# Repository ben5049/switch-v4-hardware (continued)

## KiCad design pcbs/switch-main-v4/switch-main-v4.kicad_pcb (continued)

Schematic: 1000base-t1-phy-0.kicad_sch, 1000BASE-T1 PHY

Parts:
C1301, C1302, C1305, C1306, C1307: 4u7; C_0402
C1303: 22p; C_0402
C1304, C1308, C1309, C1310, C1311, C1313, C1314, C1315, C1316, C1317, C1318, C1319, C1320: 100n; C_0402
C1312, C1321: 10u; C_0402
C1322: 10u; C_0402; not fitted
L1301: 78438313015; L_Wurth_WE-MAIA-1610; Part Number 78438313015
Q1301: DMN21D2UFB-7B; DMN21D2UFB7B; Mouser Part Number 621-DMN21D2UFB-7B
Q1302: DMP21D0UFB-7B; DMP21D0UFB7B; Mouser Part Number 621-DMP21D0UFB-7B
R1301, R1310: 4k7; R_0402
R1302: 10k; R_0402; not fitted
R1304: 4k7; R_0402; not fitted
R1305: 180k; R_0402
R1306: 360k; R_0402
R1307: 4k99; R_0402
R1308: 1k; R_0402
R1309: 47k; R_0402
TP1301, TP1302: 1.5mm; TestPoint_Pad_D1.5mm
U1301: TPS62290TDRVRQ1; SON65P200X200X80-7N; Mouser Part Number 595-TPS62290TDRVRQ1
U1302: 88Q2112-A2-NYD2A000-P123; 88Q2112

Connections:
+1V8: C1309.1, C1311.1, C1312.1, C1313.1, C1315.1, C1317.1, C1319.1, C1321.1, R1302.2, U1302.9 (AVDD18), U1302.24 (VDDO), U1302.33 (AVDD18), U1302.40 (VDDO); also elsewhere on the board
+3V3: C1301.1, C1302.1, C1308.1, C1310.1, U1301.2 (MODE), U1301.5 (VIN), U1302.6 (AVDD33); also elsewhere on the board
+3V3_AON: C1314.1, Q1302.2 (S), R1309.2, U1302.46 (VLPR); also elsewhere on the board
/CDNs & PoDL/MDI0_IN.TRXN: U1302.5 (MDIN); also elsewhere on the board
/CDNs & PoDL/MDI0_IN.TRXP: U1302.4 (MDIP); also elsewhere on the board
/PHYs/1000BASE-T1 PHY 0/0V9: C1303.1, C1305.1, C1306.1, C1307.1, C1316.1, C1318.1, C1320.1, L1301.2, R1305.1, TP1301.1 (1_1), U1302.17 (DVDD), U1302.43 (DVDD)
/PHYs/1000BASE-T1 PHY 0/CLKIN: C1304.2; also elsewhere on the board
/PHYs/1000BASE-T1 PHY 0/FB: C1303.2, R1305.2, R1306.1, U1301.3 (FB)
/PHYs/1000BASE-T1 PHY 0/GPIO: U1302.42 (GPIO/PHYAD2)
/PHYs/1000BASE-T1 PHY 0/INH: Q1302.3 (D), U1301.4 (EN); also elsewhere on the board
/PHYs/1000BASE-T1 PHY 0/INH_G: Q1301.1 (G), R1308.1
/PHYs/1000BASE-T1 PHY 0/INH_OUT: R1308.2, U1302.45 (INH)
/PHYs/1000BASE-T1 PHY 0/MDC: U1302.38 (MDC); also elsewhere on the board
/PHYs/1000BASE-T1 PHY 0/MDIO: U1302.39 (MDIO); also elsewhere on the board
/PHYs/1000BASE-T1 PHY 0/RSET: R1307.2, U1302.1 (RSET)
/PHYs/1000BASE-T1 PHY 0/SW: L1301.1, U1301.1 (SW)
/PHYs/1000BASE-T1 PHY 0/XTAL_IN: C1304.1, U1302.12 (XTAL_IN)
/PHYs/1000BASE-T1 PHY 0/~INH: Q1301.3 (D), Q1302.1 (G), R1309.1
/PHYs/1000BASE-T1 PHY 0/~RST: U1302.36 (~RST); also elsewhere on the board
/PHYs/WAKE: U1302.44 (WAKE_IN); also elsewhere on the board
/PHYs/xMII0.RX_CLK: U1302.23 (RCLK); also elsewhere on the board
/PHYs/xMII0.RX_CTL: R1301.2, U1302.22 (RXC); also elsewhere on the board
/PHYs/xMII0.RX_D0: U1302.21 (RXD0/PHYAD0); also elsewhere on the board
/PHYs/xMII0.RX_D1: U1302.20 (RXD1/PHYAD1); also elsewhere on the board
/PHYs/xMII0.RX_D2: R1310.2, U1302.19 (RXD2/MODE0); also elsewhere on the board
/PHYs/xMII0.RX_D3: U1302.18 (RXD3/MODE1); also elsewhere on the board
/PHYs/xMII0.TX_CLK: U1302.25 (TCLK); also elsewhere on the board
/PHYs/xMII0.TX_CTL: U1302.26 (TXC); also elsewhere on the board
/PHYs/xMII0.TX_D0: U1302.27 (TXD0); also elsewhere on the board
/PHYs/xMII0.TX_D1: U1302.28 (TXD1); also elsewhere on the board
/PHYs/xMII0.TX_D2: U1302.29 (TXD2); also elsewhere on the board
/PHYs/xMII0.TX_D3: U1302.30 (TXD3); also elsewhere on the board
/PHYs/~PHY0_INT: U1302.37 (~INT); also elsewhere on the board
GND1: C1301.2, C1302.2, C1305.2, C1306.2, C1307.2, C1308.2, C1309.2, C1310.2, C1311.2, C1312.2, C1313.2, C1314.2, C1315.2, C1316.2, C1317.2, C1318.2, C1319.2, C1320.2, C1321.2, C1322.2, Q1301.2 (S), R1301.1, R1304.1, R1306.2, R1307.1, R1310.1, TP1302.1 (1_1), U1301.6 (GND), U1301.7 (EP), U1302.11 (VSSC), U1302.49 (VSS); also elsewhere on the board

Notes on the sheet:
AVDD18: 145mA Typ 152mA Max
RSET Must be 1% tolerance
Use high quality, low ESR (<50mΩ) capacitors such as GRM155R61A475ME02
Internal GPIO pullups needed for ~{INT}.
Populating strapping pulldowns means that bit of the PHY address or mode will be 1.
AVDD33: 25mA Typ 27mA Max
VDDO: 18.6mA Typ
DVDD: 202mA Typ 359mA Max
This INH circuit is non-standard, and requires testing.
MODE[1:0] = 0x00 means the PHY will start as a 100BASE-T1 master, 0x01 means 100BASE-T1 slave.
Maximum allowed noise on any supply is 50mV peak to peak

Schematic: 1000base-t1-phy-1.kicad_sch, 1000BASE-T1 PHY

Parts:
C1401, C1402, C1405, C1406, C1407: 4u7; C_0402
C1403: 22p; C_0402
C1404, C1408, C1409, C1410, C1411, C1413, C1414, C1415, C1416, C1417, C1418, C1419, C1420: 100n; C_0402
C1412, C1421: 10u; C_0402
C1422: 10u; C_0402; not fitted
L1401: 78438313015; L_Wurth_WE-MAIA-1610; Part Number 78438313015
Q1401: DMN21D2UFB-7B; DMN21D2UFB7B; Mouser Part Number 621-DMN21D2UFB-7B
Q1402: DMP21D0UFB-7B; DMP21D0UFB7B; Mouser Part Number 621-DMP21D0UFB-7B
R1401, R1403: 4k7; R_0402
R1402: 10k; R_0402; not fitted
R1404: 4k7; R_0402; not fitted
R1405: 180k; R_0402
R1406: 360k; R_0402
R1407: 4k99; R_0402
R1408: 1k; R_0402
R1409: 47k; R_0402
TP1401, TP1402: 1.5mm; TestPoint_Pad_D1.5mm
U1401: TPS62290TDRVRQ1; SON65P200X200X80-7N; Mouser Part Number 595-TPS62290TDRVRQ1
U1402: 88Q2112-A2-NYD2A000-P123; 88Q2112

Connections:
+1V8: C1409.1, C1411.1, C1412.1, C1413.1, C1415.1, C1417.1, C1419.1, C1421.1, R1402.2, U1402.9 (AVDD18), U1402.24 (VDDO), U1402.33 (AVDD18), U1402.40 (VDDO); also elsewhere on the board
+3V3: C1401.1, C1402.1, C1408.1, C1410.1, U1401.2 (MODE), U1401.5 (VIN), U1402.6 (AVDD33); also elsewhere on the board
+3V3_AON: C1414.1, Q1402.2 (S), R1409.2, U1402.46 (VLPR); also elsewhere on the board
/CDNs & PoDL/MDI1_IN.TRXN: U1402.5 (MDIN); also elsewhere on the board
/CDNs & PoDL/MDI1_IN.TRXP: U1402.4 (MDIP); also elsewhere on the board
/PHYs/1000BASE-T1 PHY 0/INH: Q1402.3 (D), U1401.4 (EN); also elsewhere on the board
/PHYs/1000BASE-T1 PHY 0/MDC: U1402.38 (MDC); also elsewhere on the board
/PHYs/1000BASE-T1 PHY 0/MDIO: U1402.39 (MDIO); also elsewhere on the board
/PHYs/1000BASE-T1 PHY 0/~RST: U1402.36 (~RST); also elsewhere on the board
/PHYs/1000BASE-T1 PHY 1/0V9: C1403.1, C1405.1, C1406.1, C1407.1, C1416.1, C1418.1, C1420.1, L1401.2, R1405.1, TP1401.1 (1_1), U1402.17 (DVDD), U1402.43 (DVDD)
/PHYs/1000BASE-T1 PHY 1/CLKIN: C1404.2; also elsewhere on the board
/PHYs/1000BASE-T1 PHY 1/FB: C1403.2, R1405.2, R1406.1, U1401.3 (FB)
/PHYs/1000BASE-T1 PHY 1/GPIO: U1402.42 (GPIO/PHYAD2)
/PHYs/1000BASE-T1 PHY 1/INH_G: Q1401.1 (G), R1408.1
/PHYs/1000BASE-T1 PHY 1/INH_OUT: R1408.2, U1402.45 (INH)
/PHYs/1000BASE-T1 PHY 1/RSET: R1407.2, U1402.1 (RSET)
/PHYs/1000BASE-T1 PHY 1/SW: L1401.1, U1401.1 (SW)
/PHYs/1000BASE-T1 PHY 1/XTAL_IN: C1404.1, U1402.12 (XTAL_IN)
/PHYs/1000BASE-T1 PHY 1/~INH: Q1401.3 (D), Q1402.1 (G), R1409.1
/PHYs/WAKE: U1402.44 (WAKE_IN); also elsewhere on the board
/PHYs/xMII1.RX_CLK: U1402.23 (RCLK); also elsewhere on the board
/PHYs/xMII1.RX_CTL: R1401.2, U1402.22 (RXC); also elsewhere on the board
/PHYs/xMII1.RX_D0: R1403.2, U1402.21 (RXD0/PHYAD0); also elsewhere on the board
/PHYs/xMII1.RX_D1: U1402.20 (RXD1/PHYAD1); also elsewhere on the board
/PHYs/xMII1.RX_D2: U1402.19 (RXD2/MODE0); also elsewhere on the board
/PHYs/xMII1.RX_D3: U1402.18 (RXD3/MODE1); also elsewhere on the board
/PHYs/xMII1.TX_CLK: U1402.25 (TCLK); also elsewhere on the board
/PHYs/xMII1.TX_CTL: U1402.26 (TXC); also elsewhere on the board
/PHYs/xMII1.TX_D0: U1402.27 (TXD0); also elsewhere on the board
/PHYs/xMII1.TX_D1: U1402.28 (TXD1); also elsewhere on the board
/PHYs/xMII1.TX_D2: U1402.29 (TXD2); also elsewhere on the board
/PHYs/xMII1.TX_D3: U1402.30 (TXD3); also elsewhere on the board
/PHYs/~PHY1_INT: U1402.37 (~INT); also elsewhere on the board
GND1: C1401.2, C1402.2, C1405.2, C1406.2, C1407.2, C1408.2, C1409.2, C1410.2, C1411.2, C1412.2, C1413.2, C1414.2, C1415.2, C1416.2, C1417.2, C1418.2, C1419.2, C1420.2, C1421.2, C1422.2, Q1401.2 (S), R1401.1, R1403.1, R1404.1, R1406.2, R1407.1, TP1402.1 (1_1), U1401.6 (GND), U1401.7 (EP), U1402.11 (VSSC), U1402.49 (VSS); also elsewhere on the board

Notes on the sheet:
Internal GPIO pullups needed for ~{INT}.
AVDD18: 145mA Typ 152mA Max
RSET Must be 1% tolerance
Use high quality, low ESR (<50mΩ) capacitors such as GRM155R61A475ME02
Populating strapping pulldowns means that bit of the PHY address or mode will be 1.
AVDD33: 25mA Typ 27mA Max
VDDO: 18.6mA Typ
DVDD: 202mA Typ 359mA Max
This INH circuit is non-standard, and requires testing.
MODE[1:0] = 0x00 means the PHY will start as a 100BASE-T1 master, 0x01 means 100BASE-T1 slave.
Maximum allowed noise on any supply is 50mV peak to peak

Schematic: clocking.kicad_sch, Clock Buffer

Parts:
C1201: 1u; C_0402
C1202: 100n; C_0402
R1201: 47k; R_0402
R1202, R1203, R1204: 22R; R_0402
TP1201: 1.5mm; TestPoint_Pad_D1.5mm
U1201: LMK1C1104DQFR; SON50P200X200X80-8N; Mouser Part Number 595-LMK1C1104DQFR

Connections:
+1V8: C1201.1, C1202.1, R1201.2, U1201.6 (VDD); also elsewhere on the board
/PHYs/1000BASE-T1 PHY 0/CLKIN: R1203.2; also elsewhere on the board
/PHYs/1000BASE-T1 PHY 1/CLKIN: R1204.2; also elsewhere on the board
/PHYs/1000BASE-T1 PHY 2/CLKIN: R1202.2; also elsewhere on the board
/PHYs/CLK_EN: R1201.1, U1201.2 (1G); also elsewhere on the board
/PHYs/CLK_IN: U1201.1 (CLKIN); also elsewhere on the board
/PHYs/Clocking/Y1: R1202.1, U1201.8 (Y1)
/PHYs/Clocking/Y2: R1203.1, U1201.5 (Y2)
/PHYs/Clocking/Y3: R1204.1, U1201.7 (Y3)
GND1: C1201.2, C1202.2, TP1201.1 (1_1), U1201.4 (GND); also elsewhere on the board

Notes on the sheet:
Source termination (place close to buffer)

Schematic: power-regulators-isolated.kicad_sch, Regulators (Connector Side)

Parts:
C701: 10u; C_0805; Voltage 50V
C702, C703, C704, C706, C711: 1u; C_0402
C705: 100n; C_0402
C707, C708, C709, C710, C712: 4u7; C_0402
L701: 74438323047; L_Wurth_WE-MAPI-2510; Part Number 74438323047
R701: 180k; R_0402
R702: 33k; R_0402
TP701, TP702: 1.5mm; TestPoint_Pad_D1.5mm
U701: TPS7B8133QDRVRQ1; SON65P200X200X80-7N; Mouser Part Number 595-TPS7B8133QDRVRQ1
U702: MAX20075DATCA/V+; SON50P300X300X80-13N
U703: NCP508MT25TBG

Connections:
+2V5_ISO: C711.1, U703.1 (VOUT); also elsewhere on the board
+3V3_ISO: C704.1, C706.1, TP701.1 (1_1), U701.6 (OUT), U703.6 (VIN); also elsewhere on the board
+6V5_ISO: C702.1, C707.1, C708.1, C709.1, C710.1, C712.1, L701.2 (w2), R701.2, TP702.1 (1_1), U701.1 (IN), U701.2 (EN), U702.9 (OUT); also elsewhere on the board
+VIN_ISO: C701.1, U702.2 (EN), U702.4 (SUP); also elsewhere on the board
/Power/2V5_ISO_EN: U703.4 (EN); also elsewhere on the board
/Power/3V3_ISO_MODE: U702.11 (SYNC); also elsewhere on the board
/Power/Regulators (Isolated)/BIAS: C703.1, U702.1 (SPS), U702.10 (BIAS)
/Power/Regulators (Isolated)/BST: C705.1, U702.3 (BST)
/Power/Regulators (Isolated)/FB: R701.1, R702.2, U702.8 (FB)
/Power/Regulators (Isolated)/LX: C705.2, L701.1, U702.5 (LX)
GND2: C701.2, C702.2, C703.2, C704.2, C706.2, C707.2, C708.2, C709.2, C710.2, C711.2, C712.2, R702.1, U701.3 (GND), U701.4 (GND), U701.7 (EP), U702.6 (PGND), U702.7 (AGND), U702.13 (GND), U703.3 (GND); also elsewhere on the board

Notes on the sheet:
2V5 Regulator
6V5 Regulator
3V3 Regulator
SYNC (MODE): - HIGH = FPWM (low ripple) - LOW = Skip (low power) (default)
Use high quality, low ESR (<50mΩ) capacitors such as GRM155R61A475ME02
Vout = 6.45V [6.25V ... 6.66V]

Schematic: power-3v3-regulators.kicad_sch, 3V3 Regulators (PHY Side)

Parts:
C401, C402: 10u; C_0805; Voltage 50V
C403: 1u; C_0402; Voltage 50V
C404, C405: 1u; C_0402
C406, C407, C408, C409, C410, C411, C412, C413, C414, C415: 4u7; C_0402
L401: 74438323022; L_Wurth_WE-MAPI-2510; Part Number 74438323022
R401, R402: 10k; R_0402
R403: 100k; R_0402
TP401, TP402, TP806: 1.5mm; TestPoint_Pad_D1.5mm
U401: TPS7B8133QDRVRQ1; SON65P200X200X80-7N; Mouser Part Number 595-TPS7B8133QDRVRQ1
U402: LMQ66420MC3RXBRQ1; LMQ664x0
U403: TPS2116DRL; SOTFL50P160X60-8N

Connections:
+3V3: C406.1, C407.1, C408.1, C409.1, C410.1, C411.1, C412.1, C413.1, C414.1, C415.1, L401.2, R403.2, TP402.1 (1_1), TP806.1 (1_1), U402.11 (VOUT/FB), U403.3 (VIN1), U403.5 (MODE); also elsewhere on the board
+3V3_AON: TP401.1 (1_1), U403.2 (VOUT), U403.7 (VOUT); also elsewhere on the board
+VIN: C401.1, C402.1, C403.1, U401.1 (IN), U401.2 (EN), U402.3 (VIN); also elsewhere on the board
/PHYs/1000BASE-T1 PHY 0/INH: R401.1, U402.1 (EN/UVLO); also elsewhere on the board
/Power/3V3 Regulators/3V3_AON_RAW: C405.1, U401.6 (OUT), U403.6 (VIN2)
/Power/3V3 Regulators/3V3_PG: R403.1, U402.14 (PG), U403.4 (PR1)
/Power/3V3 Regulators/SW: L401.1, U402.7 (SW)
/Power/3V3 Regulators/VCC: C404.1, U402.10 (VCC)
/Power/3V3_AON_ST: U403.8 (ST); also elsewhere on the board
/Power/3V3_MODE: R402.1, U402.13 (MODE/SYNC); also elsewhere on the board
GND1: C401.2, C402.2, C403.2, C404.2, C405.2, C406.2, C407.2, C408.2, C409.2, C410.2, C411.2, C412.2, C413.2, C414.2, C415.2, R401.2, R402.2, U401.3 (GND), U401.4 (GND), U401.7 (EP), U402.6 (PGND), U402.15 (GND/DAP), U403.1 (GND); also elsewhere on the board

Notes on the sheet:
3V3 Always on supply
3V3 Main Regulator
PR1 > 1V => VOUT = VIN1 PR1 < 1V => VOUT = VIN2
EN is set high by PHY INH outputs
Use high quality, low ESR (<50mΩ) capacitors such as GRM155R61A475ME02
2A Max
3V3_AON switchover to use most efficient supply.
MODE is auto by default. Setting MODE high means a lower output ripple which is necessary for the ethernet PHYs.
3V3_AON_ST Needs an MCU internal pullup
150mA Max

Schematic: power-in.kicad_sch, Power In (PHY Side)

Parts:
C301: 100n; C_0603; Voltage 100V
D301: SZESD7241N2T5G; SZESD7462N2T5G; Mouser Part Number 863-SZESD7241N2T5G
J301: MKXS1-1 Power Input; 10132797-031100LF
R301: 120k; R_0402
R302: 10k; R_0402
R303: 4k7; R_0402
R304: 47k; R_0402
R305, R306, R307: 100k; R_0402
R309: 5k6; R_0402
U301: TVS3301DRBR; SON65P300X300X100-9N-D
U302: TPS26600RHFR; QFN50P400X500X100-25N-D; Mouser Part Number 595-TPS26601RHFR

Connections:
+VIN: R307.2, U302.23 (OUT_1), U302.24 (OUT_2); also elsewhere on the board
/Power/Power In/EFUSE_IMON: R305.2, R306.2, U302.18 (IMON)
/Power/Power In/ILIM: R304.2, U302.19 (ILIM)
/Power/Power In/OVP: R302.2, R303.1, U302.12 (OVP)
/Power/Power In/RTN: R303.2, R304.1, R305.1, U302.15 (RTN), U302.25 (EP)
/Power/Power In/UVLO: R301.2, R302.1, U302.10 (UVLO)
/Power/Power In/VIN_RAW: C301.2, D301.2 (A2), J301.1 (V+), J301.2 (V+), J301.3 (V+), J301.4 (V+), J301.5 (V+), J301.6 (V+), J301.25 (V+), J301.26 (V+), J301.27 (V+), J301.28 (V+), J301.29 (V+), J301.30 (V+), R301.1, U301.1 (IN), U301.2 (IN), U301.3 (IN), U301.4 (IN), U302.8 (IN_1), U302.9 (IN_2)
/Power/Power In/~FLT: U302.22 (~FLT)
/Power/VIN_IMON: R306.1; also elsewhere on the board
/Power/VIN_VMON: R307.1, R309.2; also elsewhere on the board
GND1: C301.1, D301.1 (A1), J301.7 (V-), J301.8 (V-), J301.9 (V-), J301.10 (V-), J301.11 (V-), J301.12 (V-), J301.19 (V-), J301.20 (V-), J301.21 (V-), J301.22 (V-), J301.23 (V-), J301.24 (V-), J301.MP1 (MP), J301.MP2 (MP), R309.1, U301.5 (GND), U301.6 (GND), U301.7 (GND), U301.8 (GND), U302.17 (GND); also elsewhere on the board

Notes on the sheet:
ESD Protection
Surge Protection
UVLO = 10.9V OVP = 34.1V
I_{OUT} = V_{IMON} / 7.84
VMON = VIN / 18.857 The 150mΩ eFuse resistance should be taken into account when calculating input power.
R_{ILIM} = 47kΩ ∴ I_{LIM} = 255mA
eFuse
TPS26600 has auto-retry when a fault occurs.

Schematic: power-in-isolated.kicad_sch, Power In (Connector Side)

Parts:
C601: 100n; C_0603; Voltage 100V
D601: SZESD7241N2T5G; SZESD7462N2T5G; Mouser Part Number 863-SZESD7241N2T5G
J601: MKXS1-1 Power Input; 10132797-031100LF
R601: 120k; R_0402
R602: 10k; R_0402
R603: 4k7; R_0402
R604, R608: 5k6; R_0402
R605: 15k; R_0402
R606, R607: 100k; R_0402
U601: TVS3301DRBR; SON65P300X300X100-9N-D
U602: TPS26600RHFR; QFN50P400X500X100-25N-D; Mouser Part Number 595-TPS26601RHFR

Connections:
+VIN_ISO: R607.2, U602.23 (OUT_1), U602.24 (OUT_2); also elsewhere on the board
/Power/Power In (Isolated)/EFUSE_IMON: R605.2, R606.2, U602.18 (IMON)
/Power/Power In (Isolated)/ILIM: R604.2, U602.19 (ILIM)
/Power/Power In (Isolated)/OVP: R602.2, R603.1, U602.12 (OVP)
/Power/Power In (Isolated)/RTN: R603.2, R604.1, R605.1, U602.15 (RTN), U602.25 (EP)
/Power/Power In (Isolated)/UVLO: R601.2, R602.1, U602.10 (UVLO)
/Power/Power In (Isolated)/VIN_RAW: C601.2, D601.2 (A2), J601.1 (V+), J601.2 (V+), J601.3 (V+), J601.4 (V+), J601.5 (V+), J601.6 (V+), J601.25 (V+), J601.26 (V+), J601.27 (V+), J601.28 (V+), J601.29 (V+), J601.30 (V+), R601.1, U601.1 (IN), U601.2 (IN), U601.3 (IN), U601.4 (IN), U602.8 (IN_1), U602.9 (IN_2)
/Power/Power In (Isolated)/~FLT: U602.22 (~FLT)
/Power/VIN_ISO_IMON: R606.1; also elsewhere on the board
/Power/VIN_ISO_VMON: R607.1, R608.2; also elsewhere on the board
GND2: C601.1, D601.1 (A1), J601.7 (V-), J601.8 (V-), J601.9 (V-), J601.10 (V-), J601.11 (V-), J601.12 (V-), J601.19 (V-), J601.20 (V-), J601.21 (V-), J601.22 (V-), J601.23 (V-), J601.24 (V-), J601.MP1 (MP), J601.MP2 (MP), R608.1, U601.5 (GND), U601.6 (GND), U601.7 (GND), U601.8 (GND), U602.17 (GND); also elsewhere on the board

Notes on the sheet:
eFuse
Surge Protection
I_{OUT} = V_{IMON} / 1.125 Can be done with integers: I_{OUT} = (V_{IMON} << 3) / 9
UVLO = 10.9V OVP = 34.1V
VMON = VIN_ISO / 18.857 The 150mΩ eFuse resistance should be taken into account when calculating input power.
TPS26600 has auto-retry when a fault occurs.
R_{ILIM} = 5k6Ω ∴ I_{LIM} = 2143mA
ESD Protection

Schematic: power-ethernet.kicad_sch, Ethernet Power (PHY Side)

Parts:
C501, C502, C503, C504, C505, C506, C509, C510, C511, C512, C513, C514: 4u7; C_0402
C507, C508: 22p; C_0402
L501, L502: 78438313015; L_Wurth_WE-MAIA-1610; Part Number 78438313015
R501: 360k; R_0402
R502, R503, R504: 180k; R_0402
TP501, TP502, TP504, TP505: 1.5mm; TestPoint_Pad_D1.5mm
U501, U502: TPS62290TDRVRQ1; SON65P200X200X80-7N; Mouser Part Number 595-TPS62290TDRVRQ1

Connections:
+1V2: C508.1, C510.1, C512.1, C514.1, L502.2, R503.1, TP502.1 (1_1), TP504.1 (1_1); also elsewhere on the board
+1V8: C507.1, C509.1, C511.1, C513.1, L501.2, R501.1, TP501.1 (1_1), TP505.1 (1_1); also elsewhere on the board
+3V3: C501.1, C502.1, C503.1, C504.1, C505.1, C506.1, U501.4 (EN), U501.5 (VIN), U502.4 (EN), U502.5 (VIN); also elsewhere on the board
/Power/Ethernet Power/FB_1V2: C508.2, R503.2, R504.1, U502.3 (FB)
/Power/Ethernet Power/FB_1V8: C507.2, R501.2, R502.1, U501.3 (FB)
/Power/Ethernet Power/SW_1V2: L502.1, U502.1 (SW)
/Power/Ethernet Power/SW_1V8: L501.1, U501.1 (SW)
GND1: C501.2, C502.2, C503.2, C504.2, C505.2, C506.2, C509.2, C510.2, C511.2, C512.2, C513.2, C514.2, R502.2, R504.2, U501.2 (MODE), U501.6 (GND), U501.7 (EP), U502.2 (MODE), U502.6 (GND), U502.7 (EP); also elsewhere on the board

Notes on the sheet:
1V8 Regulator
1V2 Regulator
Use high quality, low ESR (<50mΩ) capacitors such as GRM155R61A475ME02

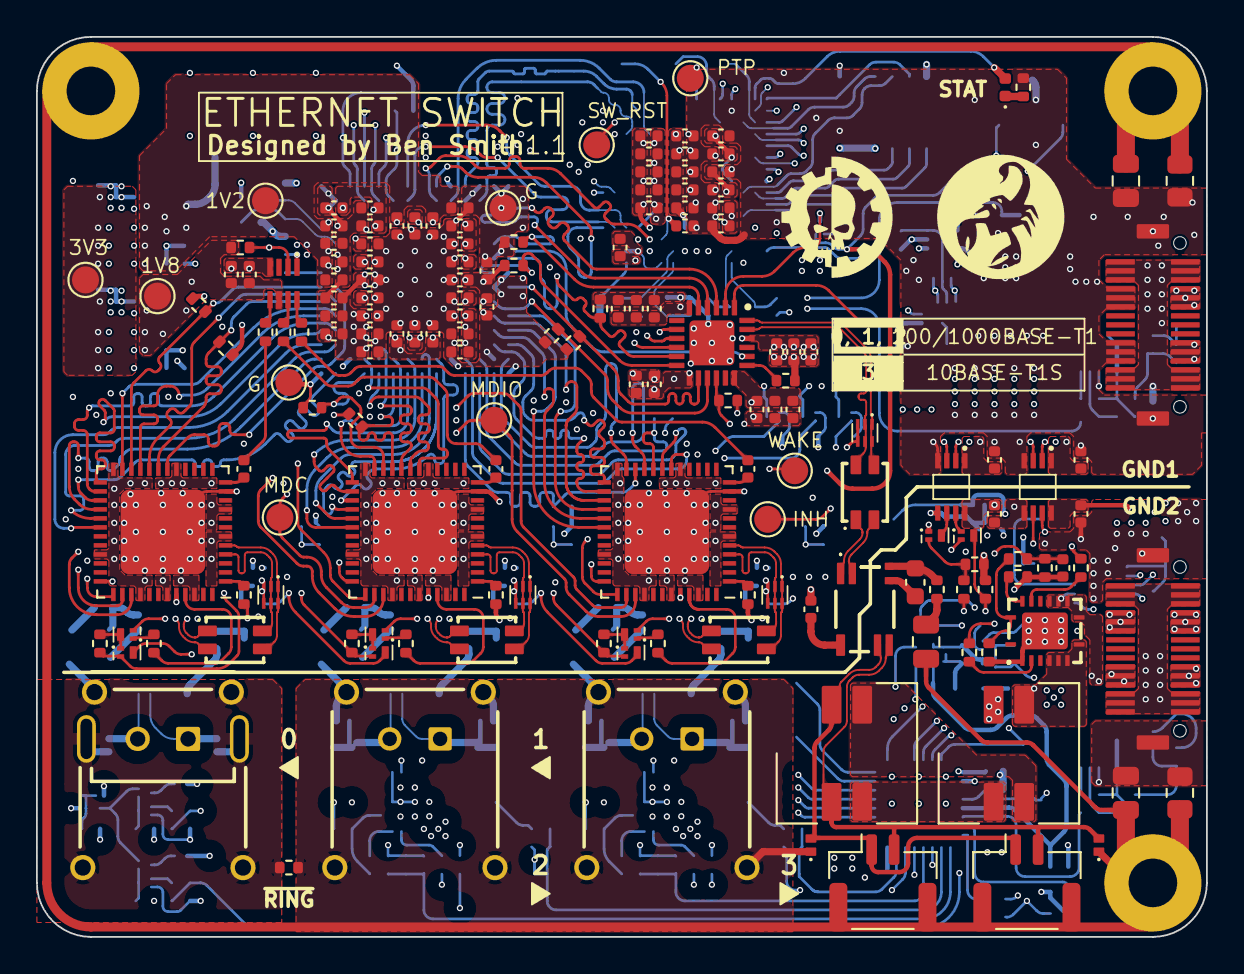
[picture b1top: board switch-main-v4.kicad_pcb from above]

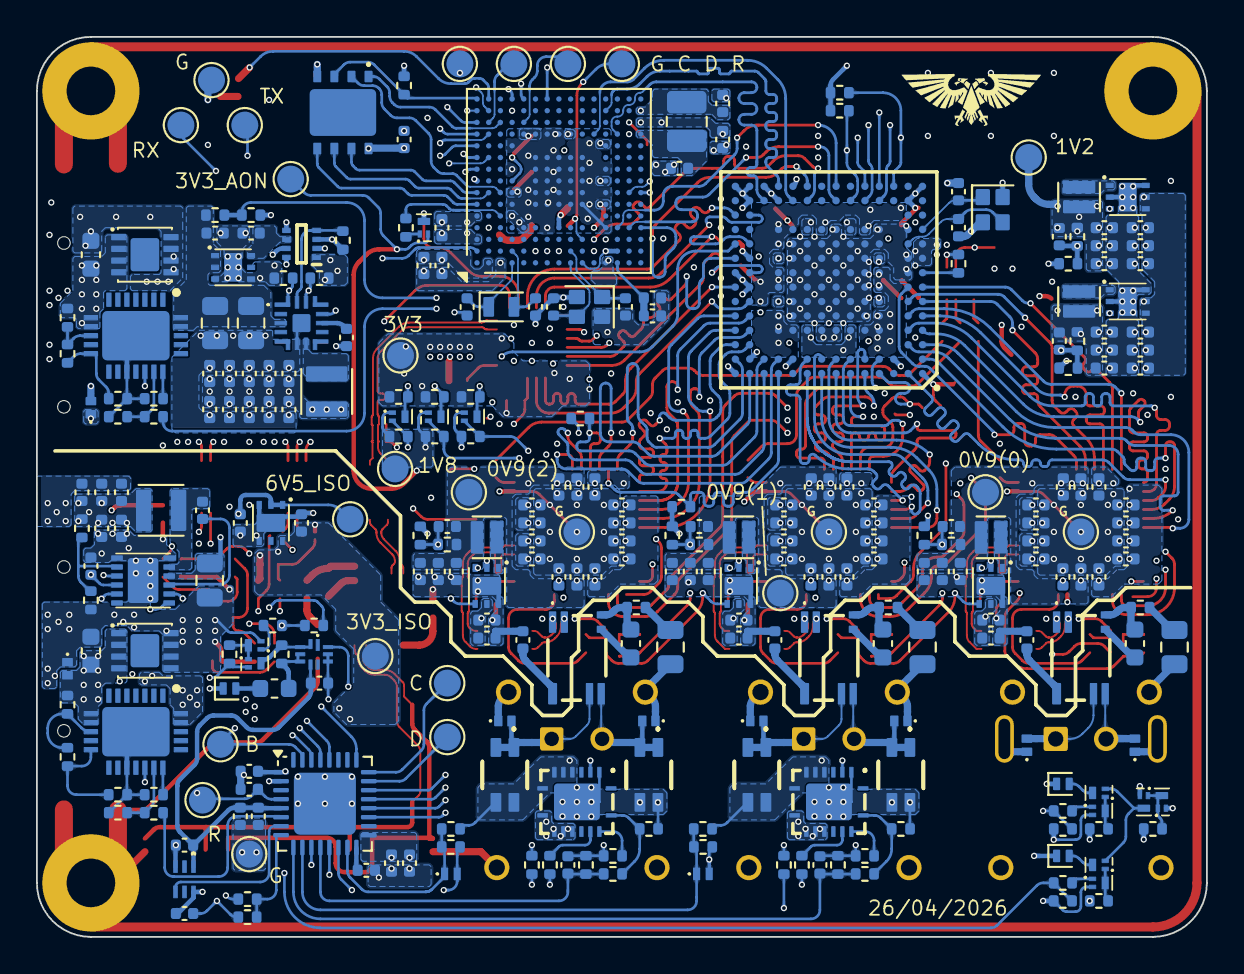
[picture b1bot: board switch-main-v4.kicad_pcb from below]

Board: 6 copper layers, 65.0 x 50.0 mm, 468 parts (301 on the bottom side), 267 nets.

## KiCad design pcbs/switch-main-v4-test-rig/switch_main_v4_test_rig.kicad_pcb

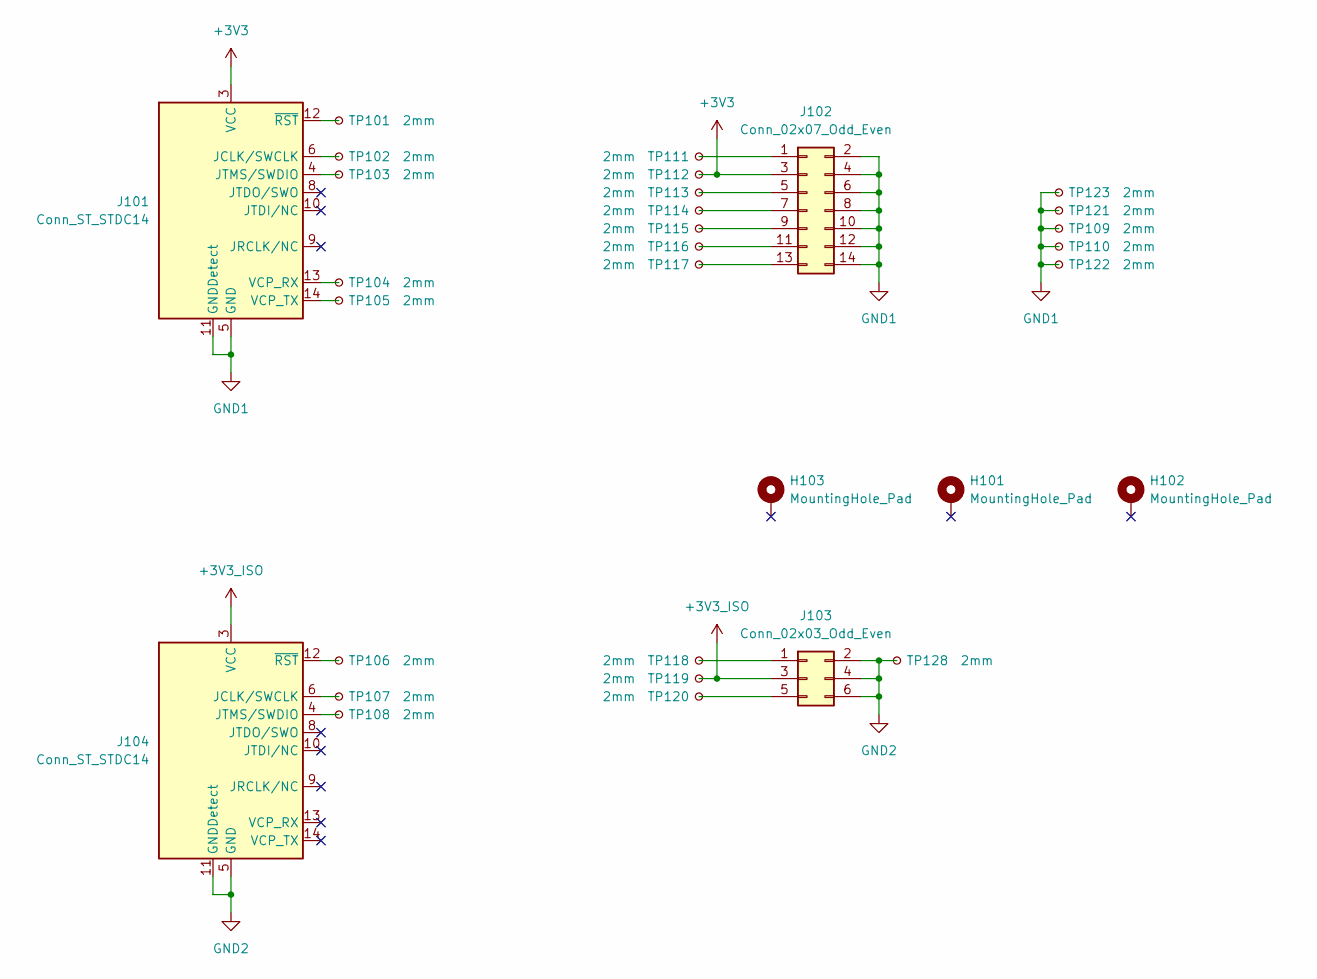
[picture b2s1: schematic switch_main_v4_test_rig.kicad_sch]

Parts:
H101, H102, H103: MountingHole_Pad; MountingHole_2.7mm_M2.5_DIN965_Pad
J101, J104: Conn_ST_STDC14; PinHeader_2x07_P1.27mm_Vertical_SMD
J102: Conn_02x07_Odd_Even; PinHeader_2x07_P2.54mm_Vertical
J103: Conn_02x03_Odd_Even; PinHeader_2x03_P2.54mm_Vertical
TP101, TP102, TP103, TP104, TP105, TP106, TP107, TP108, TP109, TP110, TP111, TP112, TP113, TP114, TP115, TP116, TP117, TP118, TP119, TP120, TP121, TP122, TP123, TP128: 2mm; TestPoint_Pad_D2.0mm

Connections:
+3V3: J101.3 (VCC), J102.3, TP112.1
+3V3_ISO: J103.3, J104.3 (VCC), TP119.1
GND1: J101.5 (GND), J101.7 (GND), J101.11 (GNDDetect), J102.2, J102.4, J102.6, J102.8, J102.10, J102.12, J102.14, TP109.1, TP110.1, TP121.1, TP122.1, TP123.1
GND2: J103.2, J103.4, J103.6, J104.5 (GND), J104.7 (GND), J104.11 (GNDDetect), TP128.1
unnamed: J101.6 (JCLK/SWCLK), TP102.1
unnamed: J101.4 (JTMS/SWDIO), TP103.1
unnamed: J101.13 (VCP_RX), TP104.1
unnamed: J101.14 (VCP_TX), TP105.1
unnamed: J101.12 (~RST), TP101.1
unnamed: J102.1, TP111.1
unnamed: J102.5, TP113.1
unnamed: J102.7, TP114.1
unnamed: J102.9, TP115.1
unnamed: J102.11, TP116.1
unnamed: J102.13, TP117.1
unnamed: J103.1, TP118.1
unnamed: J103.5, TP120.1
unnamed: J104.6 (JCLK/SWCLK), TP107.1
unnamed: J104.4 (JTMS/SWDIO), TP108.1
unnamed: J104.12 (~RST), TP106.1

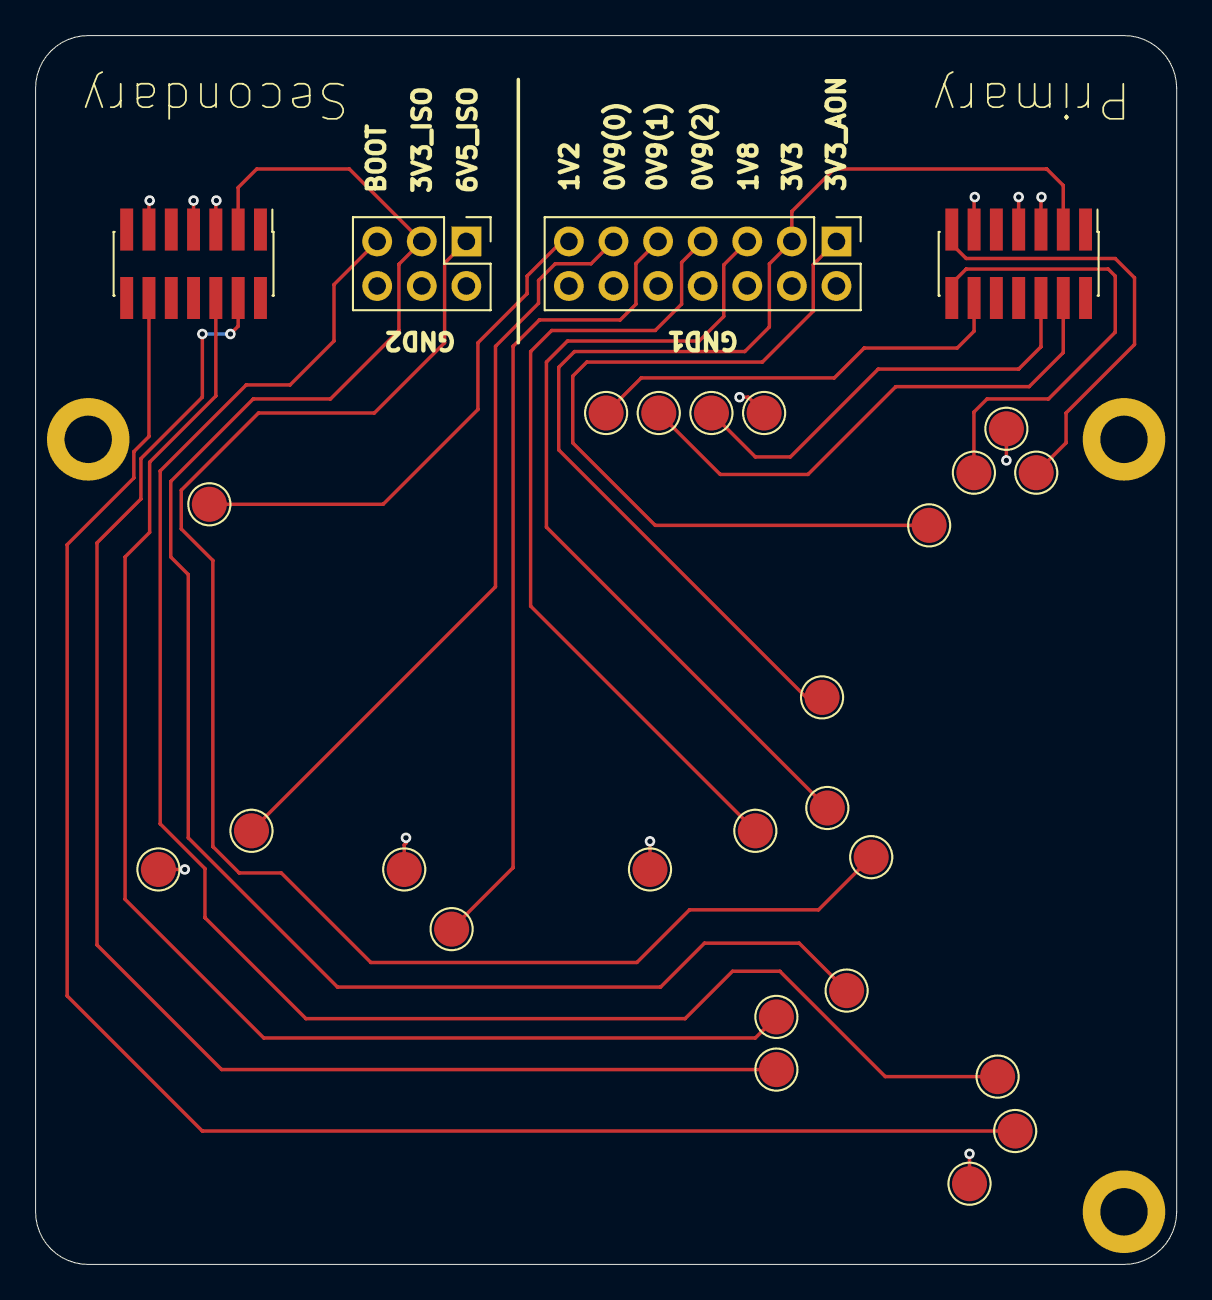
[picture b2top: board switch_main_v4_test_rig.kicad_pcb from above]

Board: 2 copper layers, 65.0 x 70.0 mm, 31 parts (0 on the bottom side), 20 nets.

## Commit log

2025-08-24 Added files
2025-10-06 Fixed mistake where RMII TX and RX signals were swapped
2025-10-09 Added component library
2025-10-09 Added test rig
2025-10-09 Updated .gitmodules
2025-11-01 Updated power connector model
2025-11-17 Added NC to unused secondary MCU pin
2025-11-30 Removed old lint warning from schematic
2025-12-25 Fixed typo in input current limit
2026-03-18 Moved component-library
2026-03-18 Tidied up repository
2026-03-19 Added errata and test rig schematics
2026-04-25 Updated to Kicad v10
